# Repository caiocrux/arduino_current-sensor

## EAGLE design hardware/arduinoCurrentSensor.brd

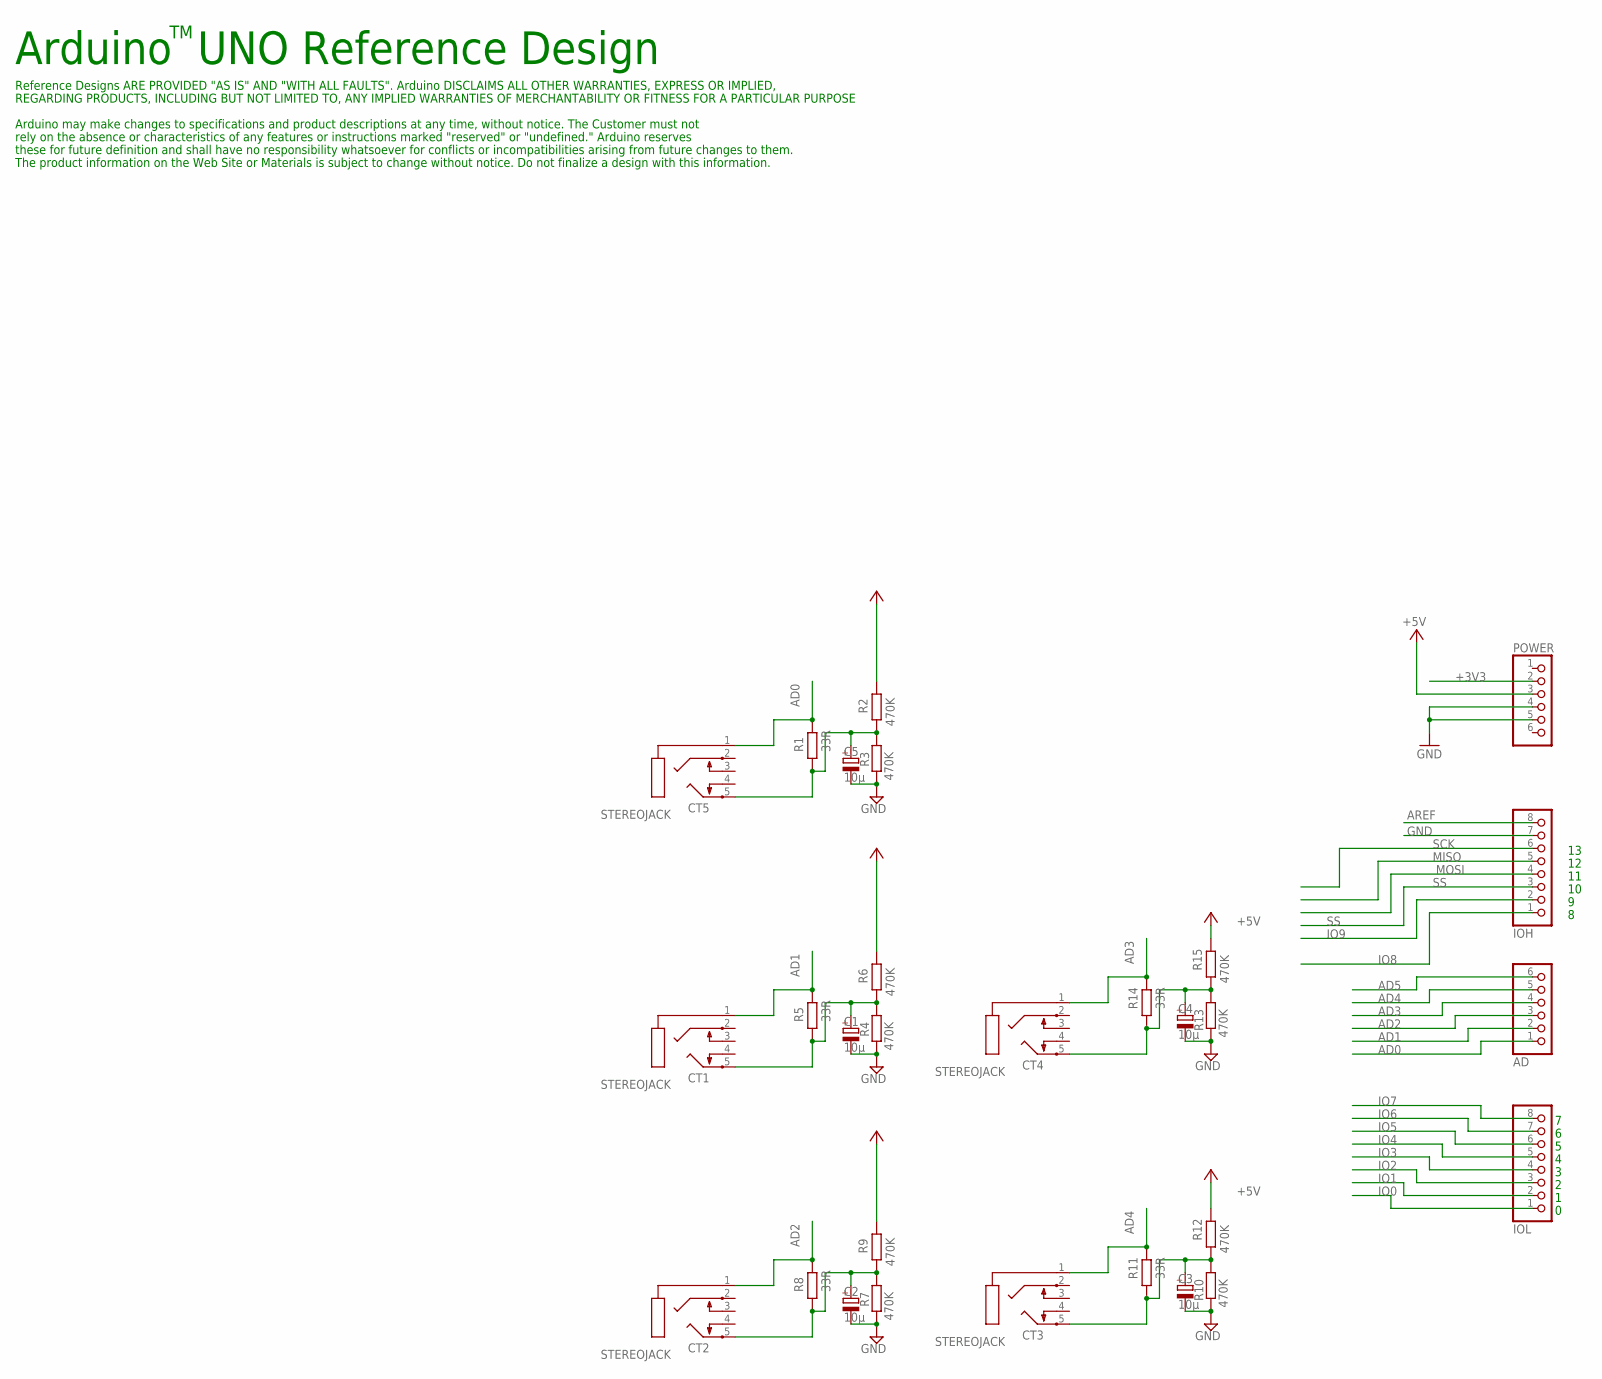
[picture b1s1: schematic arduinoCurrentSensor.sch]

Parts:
AD: PINHD-1X6; 1X06
C1, C2, C3, C4, C5: 10µ; E2-5
CT1, CT2, CT3, CT4, CT5: STEREOJACK; STX3100
IOH: PINHD-1X8; 1X08
IOL: PINHD-1X8; 1X08
POWER: PINHD-1X6; 1X06
R1, R5, R8, R11, R14: 33R; 0204/7
R2, R3, R4, R6, R7, R9, R10, R12, R13, R15: 470K; 0204/7

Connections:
+3V3: POWER.2
+5V: POWER.3, R2.2, R6.2, R9.2, R12.2, R15.2
AD0: AD.1, CT5.1, R1.2
AD1: AD.2, CT1.1, R5.2
AD2: AD.3, CT2.1, R8.2
AD3: AD.4, CT4.1, R14.2
AD4: AD.5, CT3.1, R11.2
AD5: AD.6
AREF: IOH.8
GND: C1.-, C2.-, C3.-, C4.-, C5.-, IOH.7, POWER.4, POWER.5, R3.2, R4.2, R7.2, R10.2, R13.2
IO0: IOL.1
IO1: IOL.2
IO2: IOL.3
IO3: IOL.4
IO4: IOL.5
IO5: IOL.6
IO6: IOL.7
IO7: IOL.8
IO8: IOH.1
IO9: IOH.2
MISO: IOH.5
MOSI: IOH.4
unnamed: C1.+, CT1.5, R4.1, R5.1, R6.1
unnamed: C2.+, CT2.5, R7.1, R8.1, R9.1
unnamed: C3.+, CT3.5, R10.1, R11.1, R12.1
unnamed: C5.+, CT5.5, R1.1, R2.1, R3.1
unnamed: C4.+, CT4.5, R13.1, R14.1, R15.1
SCK: IOH.6
SS: IOH.3

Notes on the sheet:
Arduino UNO Reference Design
Reference Designs ARE PROVIDED "AS IS" AND "WITH ALL FAULTS". Arduino DISCLAIMS ALL OTHER WARRANTIES, EXPRESS OR IMPLIED,
Arduino may make changes to specifications and product descriptions at any time, without notice. The Customer must not
REGARDING PRODUCTS, INCLUDING BUT NOT LIMITED TO, ANY IMPLIED WARRANTIES OF MERCHANTABILITY OR FITNESS FOR A PARTICULAR PURPOSE
rely on the absence or characteristics of any features or instructions marked "reserved" or "undefined." Arduino reserves
these for future definition and shall have no responsibility whatsoever for conflicts or incompatibilities arising from future changes to them.
The product information on the Web Site or Materials is subject to change without notice. Do not finalize a design with this information.

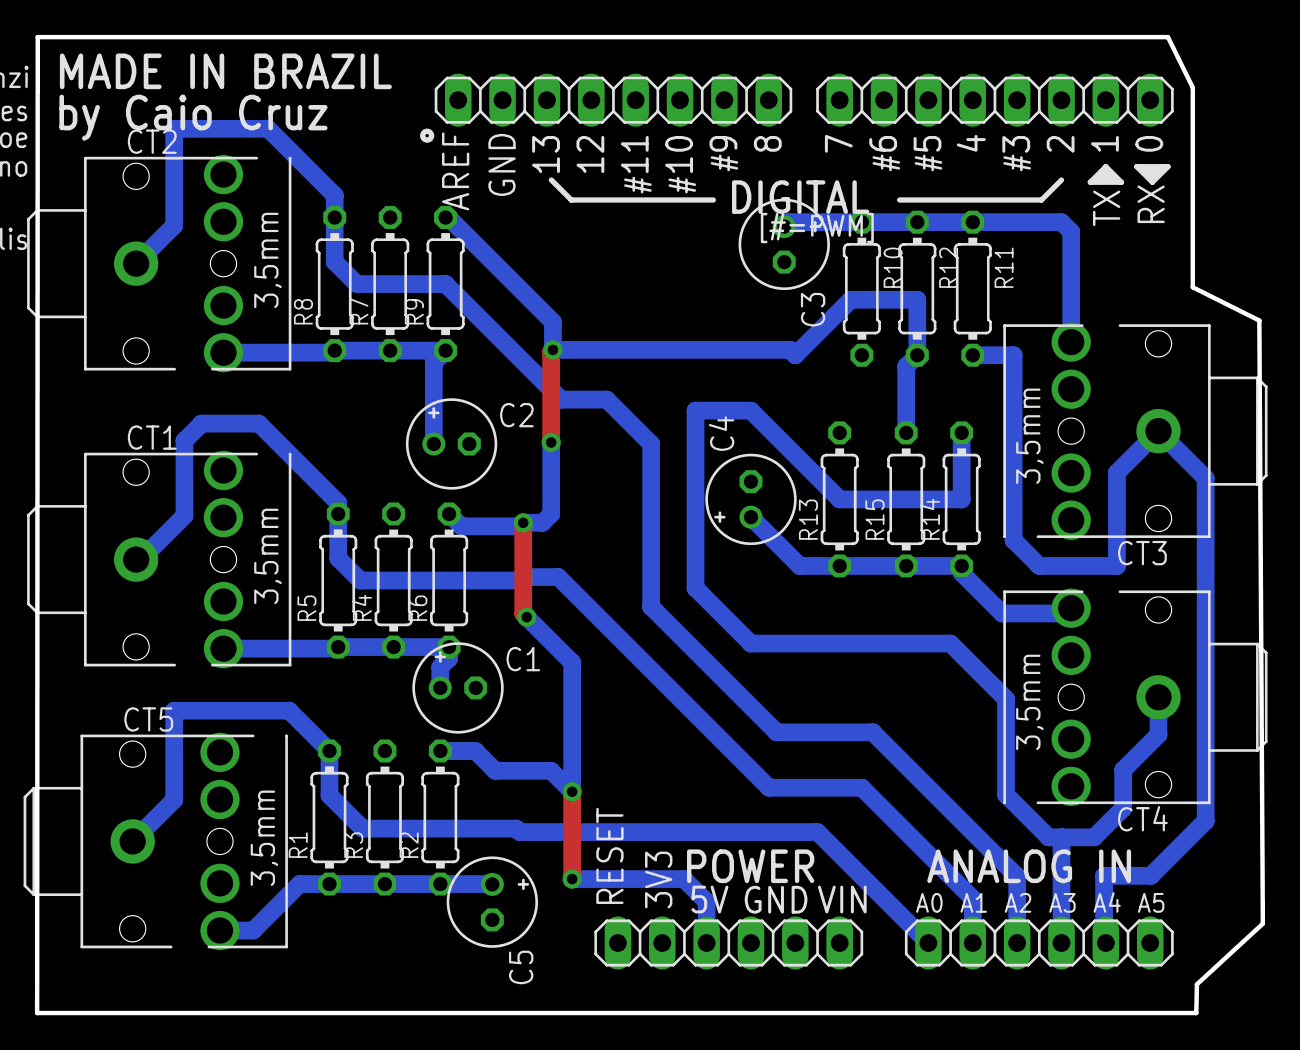
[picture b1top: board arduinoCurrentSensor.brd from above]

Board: 2 copper layers, 70.2 x 55.9 mm, 29 parts (0 on the bottom side), 12 nets.

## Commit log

2019-07-05 first version of shield
2019-07-19 removed the old files
2019-07-19 the correct version of hardware
2019-07-22 added a new topic to change the value of voltage and remove some debug information
2019-07-22 added the box
2019-07-23 added the topic to inform IP to application.Also, now is possible to change the IP using the app
